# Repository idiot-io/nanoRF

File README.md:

# nano24rf

should look something like this with nano on top, here is rev3, waiting for rev4 board to arrive from elecrow

##galleries
[Tshield nano24RF - pcb ver2](https://goo.gl/photos/zeQ4RWo6FQgi1pi57)  
[Tshield nano24RF - etching](https://goo.gl/photos/ZEXhPJtmmUaZaXrM9)

##rev4

##rev3

##rev2

##REV1

##sketch 0

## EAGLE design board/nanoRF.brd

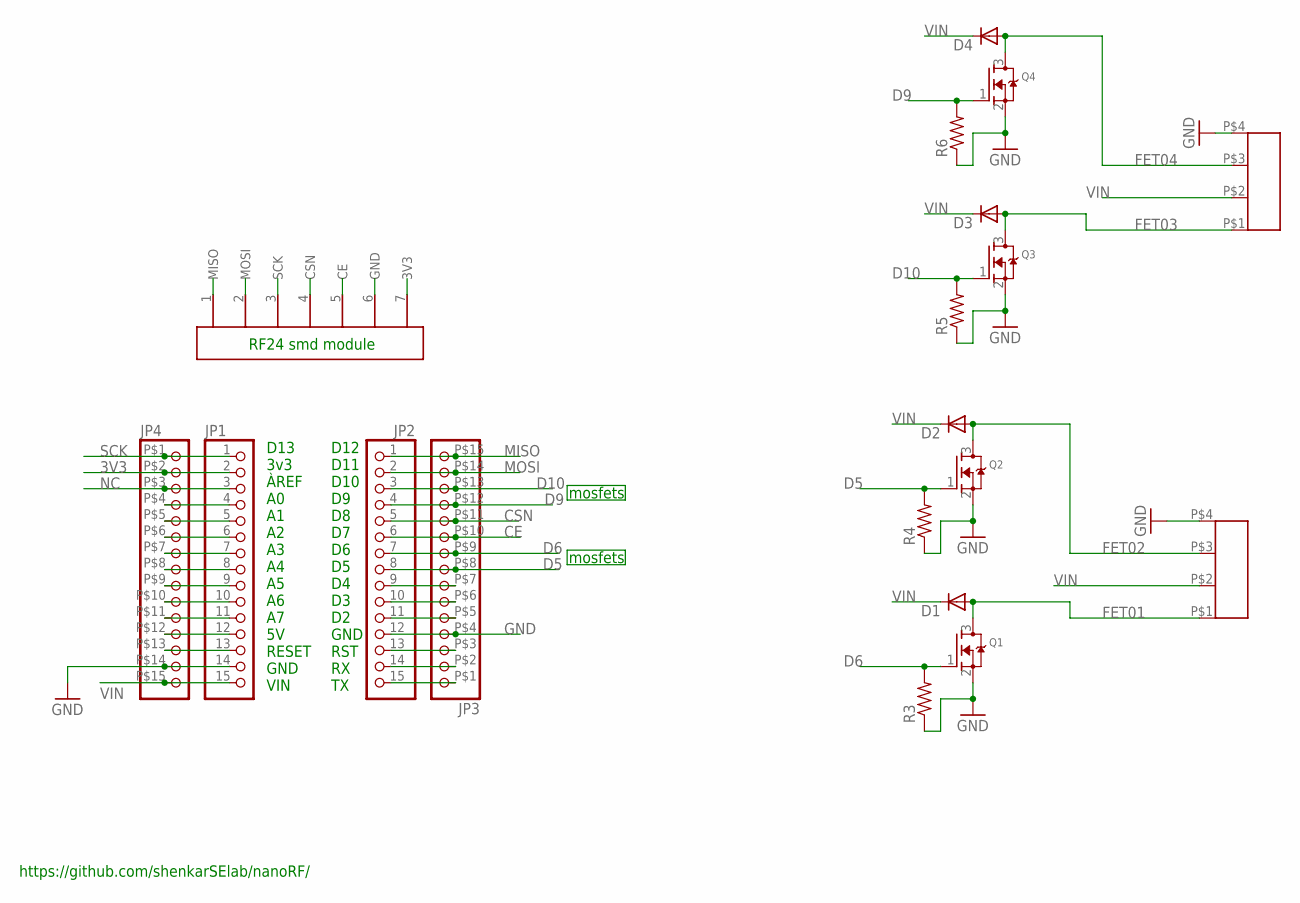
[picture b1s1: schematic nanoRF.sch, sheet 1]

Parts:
D1, D2, D3, D4: DIODE-DO-214AC; DO-214AC
JP1, JP2: HEADER-1X15RND; 1X15_ROUND_70
JP3, JP4: HEADER-1X15LONG; 1X15_LONG
MOSFET-12, MOSFET-34: FATPAD4LONG; FATFAD4-LONG
Q1, Q2, Q3, Q4: MOSFET-NWAVE; SOT23-W
R3, R4, R5, R6: RESISTOR0805-RES; 0805
RF24: 1X7-SMDPADS; SMD1,27-2,54

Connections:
3V3: JP1.2, JP4.P$2 (2), RF24.7 (3V3)
CE: JP2.6, JP3.P$10 (10), RF24.5 (CE)
CSN: JP2.5, JP3.P$11 (11), RF24.4 (CSN)
D5: JP2.8, JP3.P$8 (8), Q2.1 (G), R4.2
D6: JP2.7, JP3.P$9 (9), Q1.1 (G), R3.2
D9: JP2.4, JP3.P$12 (12), Q4.1 (G), R6.2
D10: JP2.3, JP3.P$13 (13), Q3.1 (G), R5.2
FET01: D1.2 (A), MOSFET-12.P$1, Q1.3 (D)
FET02: D2.2 (A), MOSFET-12.P$3, Q2.3 (D)
FET03: D3.2 (A), MOSFET-34.P$1, Q3.3 (D)
FET04: D4.2 (A), MOSFET-34.P$3, Q4.3 (D)
GND: JP1.14, JP2.12, JP3.P$4 (4), JP4.P$14 (14), MOSFET-12.P$4, MOSFET-34.P$4, Q1.2 (S), Q2.2 (S), Q3.2 (S), Q4.2 (S), R3.1, R4.1, R5.1, R6.1, RF24.6 (GND)
MISO: JP2.1, JP3.P$15 (15), RF24.1 (MISO)
MOSI: JP2.2, JP3.P$14 (14), RF24.2 (MOSI)
unnamed: JP1.4, JP4.P$4 (4)
unnamed: JP1.5, JP4.P$5 (5)
unnamed: JP1.6, JP4.P$6 (6)
unnamed: JP1.7, JP4.P$7 (7)
unnamed: JP1.8, JP4.P$8 (8)
unnamed: JP1.9, JP4.P$9 (9)
unnamed: JP1.10, JP4.P$10 (10)
unnamed: JP1.11, JP4.P$11 (11)
unnamed: JP1.12, JP4.P$12 (12)
unnamed: JP1.13, JP4.P$13 (13)
unnamed: JP2.15, JP3.P$1 (1)
unnamed: JP2.14, JP3.P$2 (2)
unnamed: JP2.13, JP3.P$3 (3)
unnamed: JP2.11, JP3.P$5 (5)
unnamed: JP2.10, JP3.P$6 (6)
unnamed: JP2.9, JP3.P$7 (7)
NC: JP1.3, JP4.P$3 (3)
SCK: JP1.1, JP4.P$1 (1), RF24.3 (SCK)
VIN: D1.1 (C), D2.1 (C), D3.1 (C), D4.1 (C), JP1.15, JP4.P$15 (15), MOSFET-12.P$2, MOSFET-34.P$2

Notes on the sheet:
D12 D11 D10 D9 D8 D7 D6 D5 D4 D3 D2 GND RST RX TX
D13 3v3 ÀREF A0 A1 A2 A3 A4 A5 A6 A7 5V RESET GND VIN
https://github.com/shenkarSElab/nanoRF/
mosfets
RF24 smd module

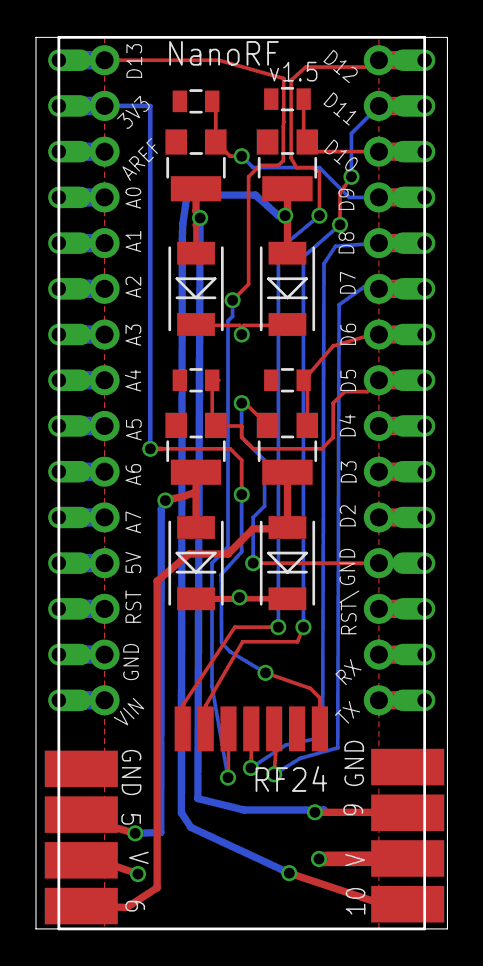
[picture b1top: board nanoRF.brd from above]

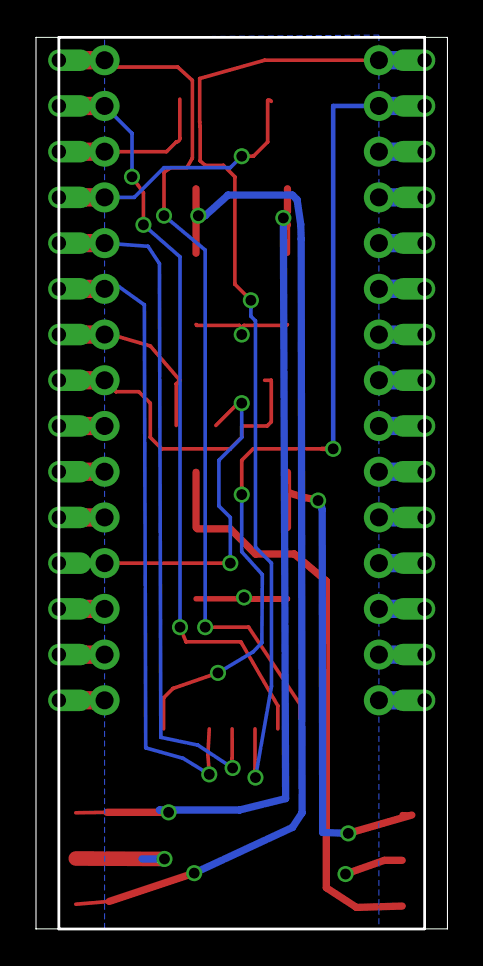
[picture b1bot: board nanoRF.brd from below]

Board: 2 copper layers, 22.7 x 49.5 mm, 19 parts (3 on the bottom side), 33 nets.

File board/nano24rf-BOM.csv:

"Qty";"Value";"Device";"Package";"Parts";"Description";"";
"4";"";"DIODE-DO-214AC";"DO-214AC";"D1, D2, D3, D4";"Various Diode Packages";"";
"2";"";"HEADER-1X15";"1X15_ROUND_70";"JP1, JP2";"1x15 Header";"";
"4";"";"MOSFET-NWAVE";"SOT23-W";"Q1, Q2, Q3, Q4";"N-Channel Mosfet";"";
"1";"";"PINHD-2X3SMT";"2X03_SMT";"JP3";"PIN HEADER";"";
"6";"";"RESISTOR0805-RES";"0805";"R1, R2, R3, R4, R5, R6";"Resistor";"";
"2";"1X3SMD";"1X3SMD";"FATPAD";"U$6, U$8";"";"";
"1";"1X7-SMDPADS";"1X7-SMDPADS";"SMD1,27-2,54";"U$7";"";"";

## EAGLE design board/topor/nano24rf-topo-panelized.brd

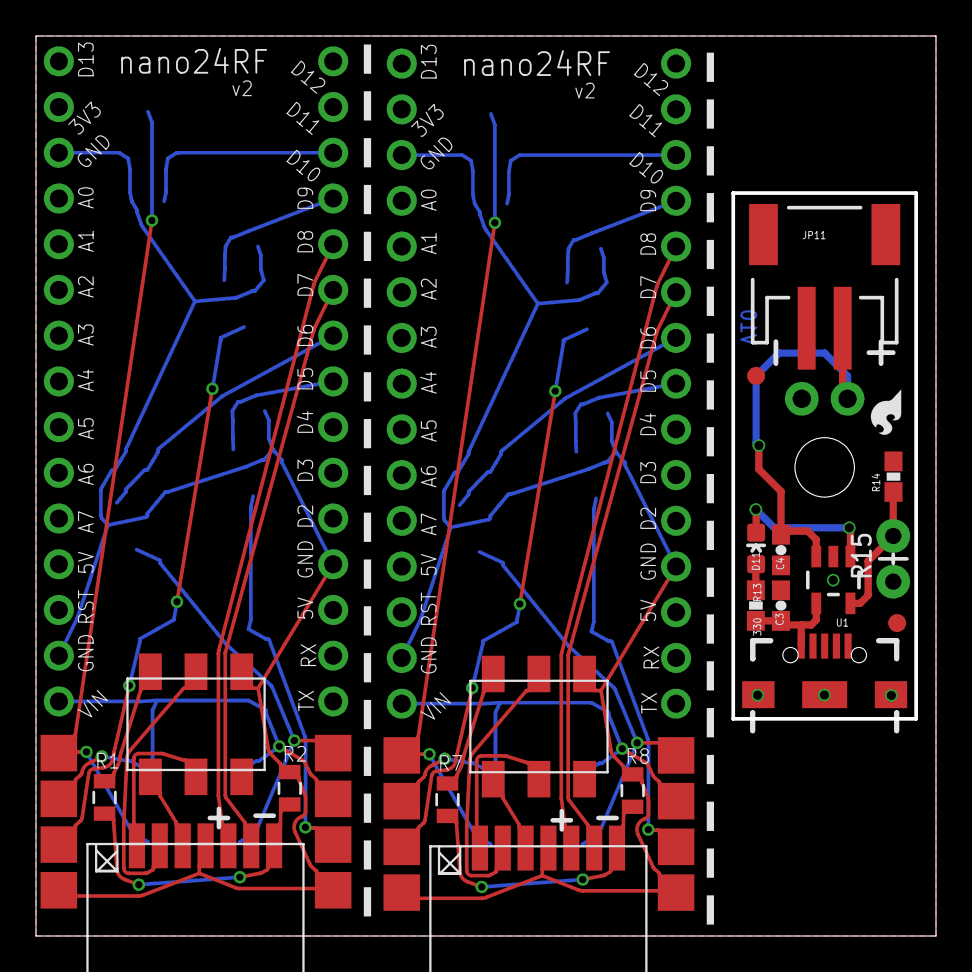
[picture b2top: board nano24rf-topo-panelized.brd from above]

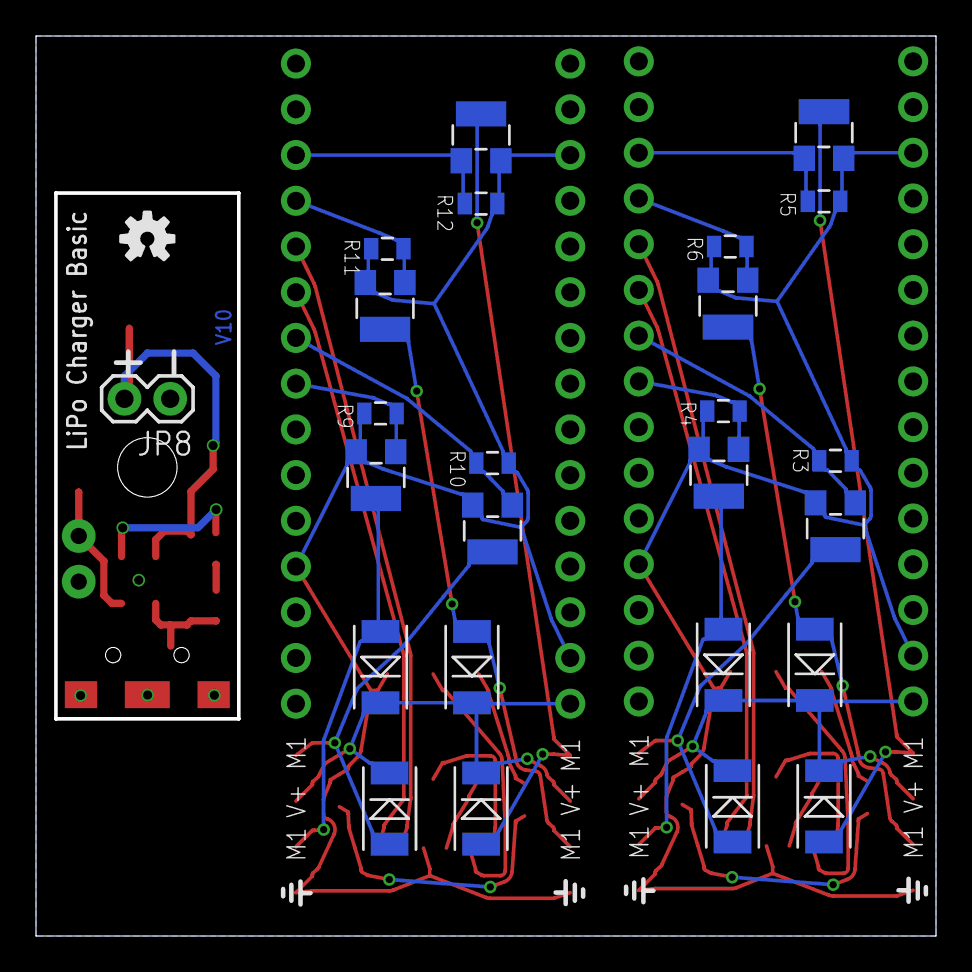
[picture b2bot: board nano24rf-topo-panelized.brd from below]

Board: 2 copper layers, 49.8 x 49.8 mm, 55 parts (26 on the bottom side), 40 nets.

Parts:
C3, C4: 4.7uF; 0603-CAP
D1, D2, D3, D4, D5, D6, D7, D8: DO-214AC
D11: RED; LED-0603
JP1, JP2, JP4, JP5: 1X15_ROUND_70
JP3, JP6: 2X03_SMT
JP7: STAND-OFF
JP8: M02PTH; 1X02
JP9: Micro USB; USB-AB-MICRO-SMD_V03
JP10, JP12: FIDUCIAL1X2; FIDUCIAL-1X2
JP11: JST; JST-2-SMD
LOGO1: OSHW-LOGOS; OSHW-LOGO-S
LOGO2: SFE_LOGO_FLAME.1_INCH; SFE_LOGO_FLAME_.1
Q1, Q2, Q3, Q4, Q5, Q6, Q7, Q8: SOT23-W
R1, R2, R3, R4, R5, R6, R7, R8, R9, R10, R11, R12: 0805
R13: 330; 0603-RES
R14: 2.0k; 0603-RES
R15: AXIAL-0.1EZ
U1: MCP73831; SOT23-5
U$1, U$7: SMD1,27-2,54
U$2, U$3, U$6, U$8: FATPAD4

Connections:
5V: JP3.2, R1.1
5V1: JP6.2, R7.1
CE: JP2.6, U$7.2
CE1: JP5.6, U$1.2
CSN: JP2.5, U$7.3
CSN1: JP5.5, U$1.3
D1: JP5.8, Q6.1, R9.2
D2: JP5.7, Q5.1, R10.2
D5: JP2.8, Q2.1, R4.2
D6: JP2.7, Q1.1, R3.2
D7: JP5.3, Q7.1, R12.2
D8: JP5.4, Q8.1, R11.2
D9: JP2.4, Q4.1, R6.2
D10: JP2.3, Q3.1, R5.2
FET01: D1.2, Q1.3, U$8.P$1
FET02: D2.2, Q2.3, U$8.P$3
FET03: D3.2, Q3.3, U$6.P$1
FET04: D4.2, Q4.3, U$6.P$3
FET05: D5.2, Q5.3, U$3.P$1
FET06: D6.2, Q6.3, U$3.P$3
FET07: D7.2, Q7.3, U$2.P$1
FET08: D8.2, Q8.3, U$2.P$3
GND: JP1.3, JP1.14, JP2.12, JP3.6, Q1.2, Q2.2, Q3.2, Q4.2, R2.1, R3.1, R4.1, R5.1, R6.1, U$6.P$4, U$7.4, U$8.P$4
GND1: JP4.3, JP4.14, JP5.12, JP6.6, Q5.2, Q6.2, Q7.2, Q8.2, R8.1, R9.1, R10.1, R11.1, R12.1, U$1.4, U$2.P$4, U$3.P$4
GND2: C3.2, C4.2, JP8.1, JP9.GND1, JP11.1, R14.2, R15.P$1, U1.2
MISO: JP3.1, U$7.5
MISO1: JP6.1, U$1.5
MOSI: JP3.4, U$7.6
MOSI1: JP6.4, U$1.6
unnamed: R7.2, R8.2, U$1.1
unnamed: D11.A, R13.1
unnamed: R1.2, R2.2, U$7.1
PROG: R14.1, R15.P$2, U1.5
SCK: JP3.3, U$7.7
SCK1: JP6.3, U$1.7
STAT: D11.C, U1.1
VCC: C4.1, JP8.2, JP11.2, U1.3
VIN: D1.1, D2.1, D3.1, D4.1, JP1.15, U$6.P$2, U$8.P$2
VIN1: D5.1, D6.1, D7.1, D8.1, JP4.15, U$2.P$2, U$3.P$2
VIN2: C3.1, JP9.VBUS1, R13.2, U1.4

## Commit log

2016-05-22 add schmea file, empty
2016-05-22 add https://github.com/cyberlink1/Arduino-Eagle-Cad-Library
2016-05-22 added arduino clone lib submodule
2016-05-22 :ignore
2016-05-22 start work on sch/brd
2016-05-22 with mini for lols
2016-05-22 remove Arduino ealecad
2016-05-23 pushed around
2016-05-23 more jump
2016-05-25 add pdf, review ver
2016-05-25 rotate labels
2016-05-25 ready for raw jumoper"
2016-05-28 removed lm317 and placed msfets on bottom
2016-05-28 wsitch!
2016-05-28 slikscreens
2016-05-31 before reomval of swith for fnr24
2016-05-31 more output
2016-06-01 gerber script and bom
2016-06-01 bord
2016-08-04 before route
2016-08-04 topoR routing
2016-08-04 fix placment or resistors
2016-08-04 added lib, need to fix volt div placment
2016-08-16 ready to grb
2016-08-18 added bom
2016-09-20 some topo
2016-09-20 added FATPAD4
2016-09-20 after topor
2016-09-20 panelized and added sparkfun lipo xchrger
2016-09-21 worm added
2016-09-21 added top mosfets, cant use cuz highet
2016-09-21 another go on the topoR
2016-09-22 added gerber worm
2016-09-22 sent to elecrow order #42345
2016-09-22 some more cleaning
2016-09-22 added rev sent to fab
2016-09-22 added GML gerber file for sub-board cuts
2016-10-17 fixed bad packges for 2x3 and smdx07
2016-10-20 routed ver3, no canstlation
2016-10-21 added gerber for cestlation fike
2016-10-21 back to round ads
2016-10-21 long pads
2016-10-21 slight schema re-arange, and gerber
2016-10-25 switched to pin11 one of the mosfet
2016-10-25 removed SPI
2016-10-25 re-routed D10 to MOSFET
2016-10-25 SCK reouted, and shoved nrf24 inside
2016-10-25 new gerber for slim design
2016-10-25 back to plated edge
2016-10-25 nice
2016-10-27 silkscreen bahh
2016-10-27 slight changes
2016-11-09 sent
2017-01-31 pushed cneter parts back
2017-01-31 board export
2017-02-06 refined edges
2017-02-06 removed extra layers
2017-02-10 sent for price quete
2017-02-12 non castlated version
2017-05-13 added media folder
2017-05-15 added example folder, with pulse sensor code
2017-05-15 working with timer1
2017-05-17 changed prj name and files to nanoRF, starting fix for AREF pin
2017-05-17 fixed Aref pin horror
2017-05-17 added interrupt explain, reducted comments
2017-05-17 sending to reciever
2017-05-17 sorta working ispuklse
2017-05-17 pulsing code
2017-05-20 gen no edge version
2017-05-20 removed reset and aref
2017-05-20 gerber no edge
2017-05-20 edge
2017-05-20 moved corner to 0,0
2017-05-20 added gerber edge
2017-05-20 added noEdge
2017-05-21 new code
2017-06-27 add to lbr the fat drill holes for swiss pinheaders
2018-05-13 revert to green ver, with gnd fix
2018-05-13 added schema
2018-05-13 gerber for edge
2018-05-13 noEdge design, with gerber files
2018-05-14 no edge v1.5
2018-05-14 new cam, both cutouts
2018-05-14 board png
2018-05-16 approved singlee boards for fab
2019-03-20 one-to-many
2019-03-20 30us jitter, same channel
2019-03-21 super lean
2019-04-03 added fast gpio
2019-04-04 switchpin.h
2019-04-11 simple works
2019-10-02 PackAgeSticky&QR
2019-10-16 NanoRFMesh
2019-10-18 cleanin
2019-10-18 folder order!
2019-10-18 zzzz
2019-10-25 test
2019-10-26 datastruct
2019-10-26 nod2
2019-10-28 NanoRFMeshNet

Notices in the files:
parts and their libraries:
SparkFun-Resistors: Licensing: Creative Commons ShareAlike 4.0 International - https://creativecommons.org/licenses/by-sa/4.0
